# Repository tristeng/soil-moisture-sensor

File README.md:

# Soil Moisture Sensor
Design of a sensor that can be used to measure soil moisture. Although these sensor designs already exist, I wanted to create a circuit such that the output signal 
used the full range of the input voltage and is directly proportional to the measured soil moisture.

## Contents
### Notebooks
The bulk of this repository is the notebook found in the notebooks directory. This can be run using [Jupyter](https://jupyter.org/).

### Eagle Files
The board and schematic designs can be found in the eagle directory.

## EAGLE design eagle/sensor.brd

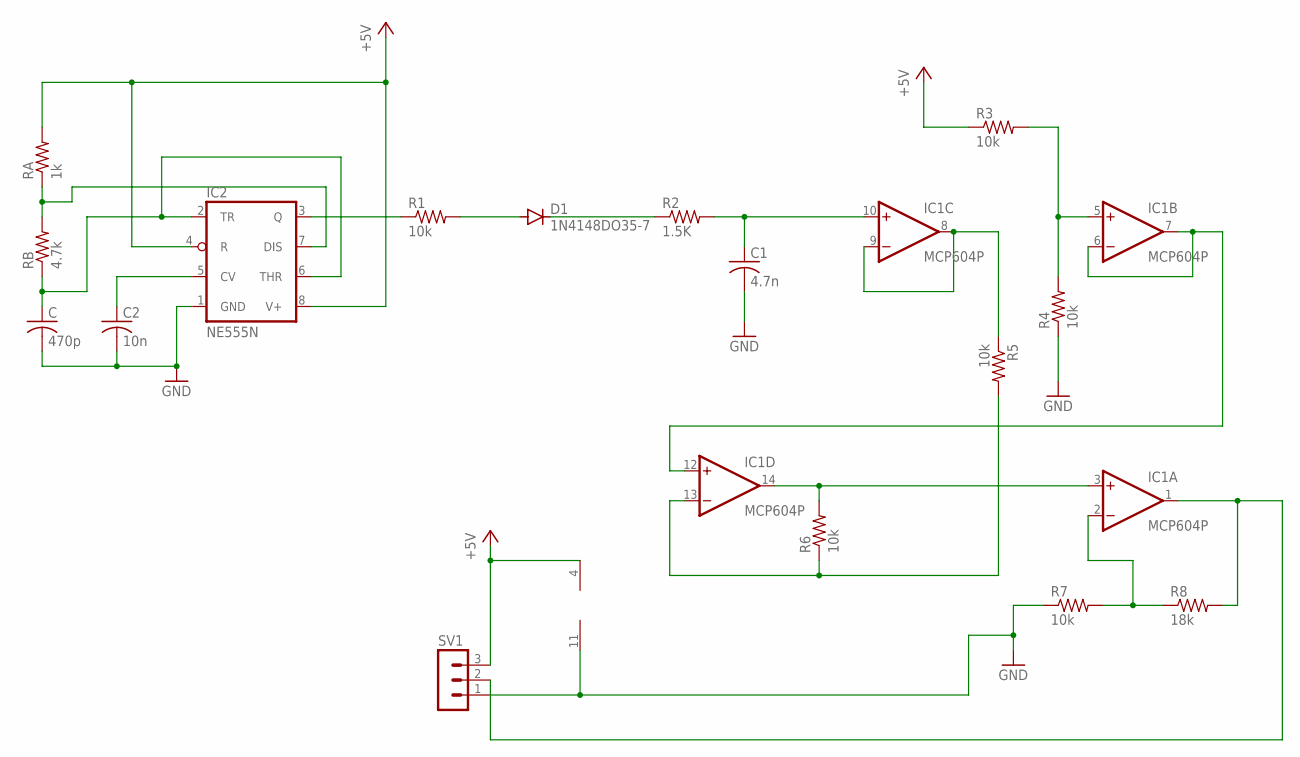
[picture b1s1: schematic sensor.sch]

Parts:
C: 470p; C025-024X044
C1: 4.7n; C025-024X044
C2: 10n; C025-024X044
D1: 1N4148DO35-7; DO35-7
IC1: MCP604P; DIL14
IC2: NE555N; DIL08
R1, R3, R4, R5, R6, R7: 10k; 0204/7
R2: 1.5K; 0204/7
R8: 18k; 0204/7
RA: 1k; 0204/7
RB: 4.7k; 0204/7
SV1: MA03-1

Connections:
+5V: IC1.4 (V+), IC2.4 (R), IC2.8 (V+), R3.1, RA.2, SV1.3
GND: C.2, C1.2, C2.2, IC1.11 (V-), IC2.1 (GND), R4.1, R7.1, SV1.1
unnamed: C2.1, IC2.5 (CV)
unnamed: C.1, IC2.2 (TR), IC2.6 (THR), RB.1
unnamed: IC2.3 (Q), R1.1
unnamed: IC2.7 (DIS), RA.1, RB.2
unnamed: D1.A, R1.2
unnamed: D1.C, R2.1
unnamed: C1.1, IC1.10 (+IN), R2.2
unnamed: IC1.13 (-IN), R5.2, R6.1
unnamed: IC1.5 (+IN), R3.2, R4.2
unnamed: IC1.6 (-IN), IC1.7 (OUT), IC1.12 (+IN)
unnamed: IC1.8 (OUT), IC1.9 (-IN), R5.1
unnamed: IC1.3 (+IN), IC1.14 (OUT), R6.2
unnamed: IC1.1 (OUT), R8.2, SV1.2
unnamed: IC1.2 (-IN), R7.2, R8.1

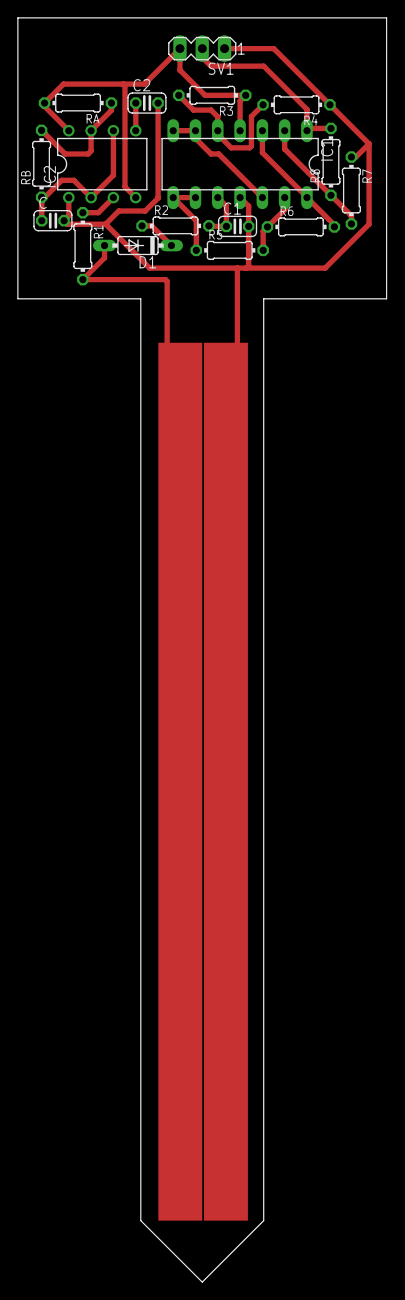
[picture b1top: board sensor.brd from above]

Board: 2 copper layers, 42.0 x 144.0 mm, 17 parts (0 on the bottom side), 16 nets.

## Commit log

2021-05-23 add license
2021-05-24 added repository readme file
